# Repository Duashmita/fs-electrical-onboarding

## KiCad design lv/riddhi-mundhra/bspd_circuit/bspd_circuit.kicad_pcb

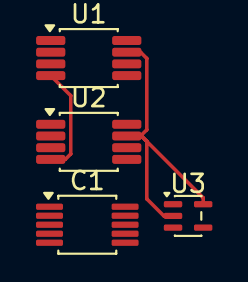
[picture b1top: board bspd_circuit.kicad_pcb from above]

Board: 2 copper layers, 4 parts (0 on the bottom side), 6 nets.

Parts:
C1: 1000; MSOP-10_3x3mm_P0.5mm
U1, U2: OPA196xDGK; VSSOP-8_3x3mm_P0.65mm
U3: TLV172IDCK; SOT-353_SC-70-5

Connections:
+3V3: U1.4 (V-), U1.7 (V+), U2.4 (V-), U2.7 (V+), U3.2 (V-), U3.5 (V+)
unnamed: C1.2, U3.4
unnamed: U1.3 (+), U2.3 (+)
unnamed: U1.2 (-), U2.2 (-)
unnamed: U1.6, U2.6
unnamed: C1.1, U3.3 (-)

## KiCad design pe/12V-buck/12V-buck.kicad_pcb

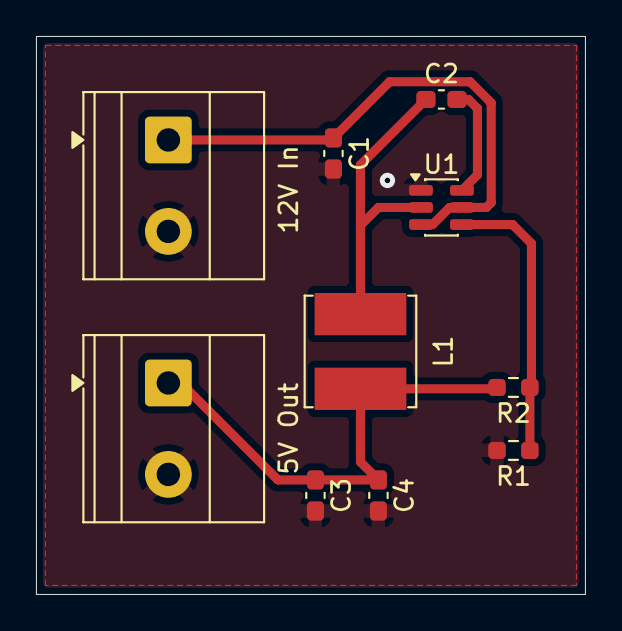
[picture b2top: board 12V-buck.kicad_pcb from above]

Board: 2 copper layers, 30.5 x 31.0 mm, 10 parts (0 on the bottom side), 6 nets.

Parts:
5V Out: 5V; TerminalBlock_Phoenix_MKDS-1,5-2-5.08_1x02_P5.08mm_Horizont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
12V In: 12V; TerminalBlock_Phoenix_MKDS-1,5-2-5.08_1x02_P5.08mm_Horizont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
C1: 10uF; C_0603_1608Metric_Pad1.08x0.95mm_HandSolder
C2: 100nF; C_0603_1608Metric_Pad1.08x0.95mm_HandSolder
C3, C4: 22uF; C_0603_1608Metric_Pad1.08x0.95mm_HandSolder
L1: 3.3uH; L_Bourns_SRN6045TA
R1: 10k; R_0603_1608Metric_Pad0.98x0.95mm_HandSolder
R2: 54.9k; R_0603_1608Metric_Pad0.98x0.95mm_HandSolder
U1: TPS563208; SOT-23-6

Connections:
+5V: 5V Out.1, C3.1, C4.1, L1.2, R2.2
+12V: 12V In.1, C1.1, U1.3 (VIN), U1.5 (EN)
GND: 5V Out.2, 12V In.2, C1.2, C3.2, C4.2, R1.2, U1.1 (GND)
unnamed: C2.1, L1.1, U1.2 (SW)
unnamed: C2.2, U1.6 (VBST)
unnamed: R1.1, R2.1, U1.4 (VFB)

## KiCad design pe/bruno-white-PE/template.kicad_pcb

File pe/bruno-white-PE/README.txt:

KiCad Local History Directory
=============================

Hello Edmund, this is the link to my google document here:

https://docs.google.com/document/d/1SfllieP0r4iqk_yWfgpT94NKgeAnDmSCqJz-1QESXFs/edit?usp=sharing

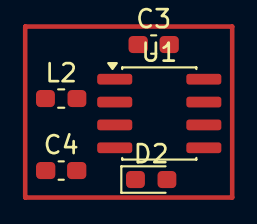
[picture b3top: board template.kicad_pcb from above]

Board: 2 copper layers, 5 parts (0 on the bottom side), 4 nets, no tracks yet.

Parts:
C3, C4: C_Small; C_0603_1608Metric_Pad1.08x0.95mm_HandSolder
D2: D_Small; D_0603_1608Metric_Pad1.05x0.95mm_HandSolder
L2: 2A; L_0603_1608Metric_Pad1.05x0.95mm_HandSolder
U1: XL1509-ADJ; SOIC-8_3.9x4.9mm_P1.27mm

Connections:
/VIN: C3.1, U1.1 (VIN)
/VOUT: C4.1, L2.2
GND: C3.2, C4.2, D2.2 (A), U1.5 (GND), U1.6 (GND), U1.7 (GND), U1.8 (GND)
unnamed: D2.1 (K), L2.1, U1.2 (OUT)

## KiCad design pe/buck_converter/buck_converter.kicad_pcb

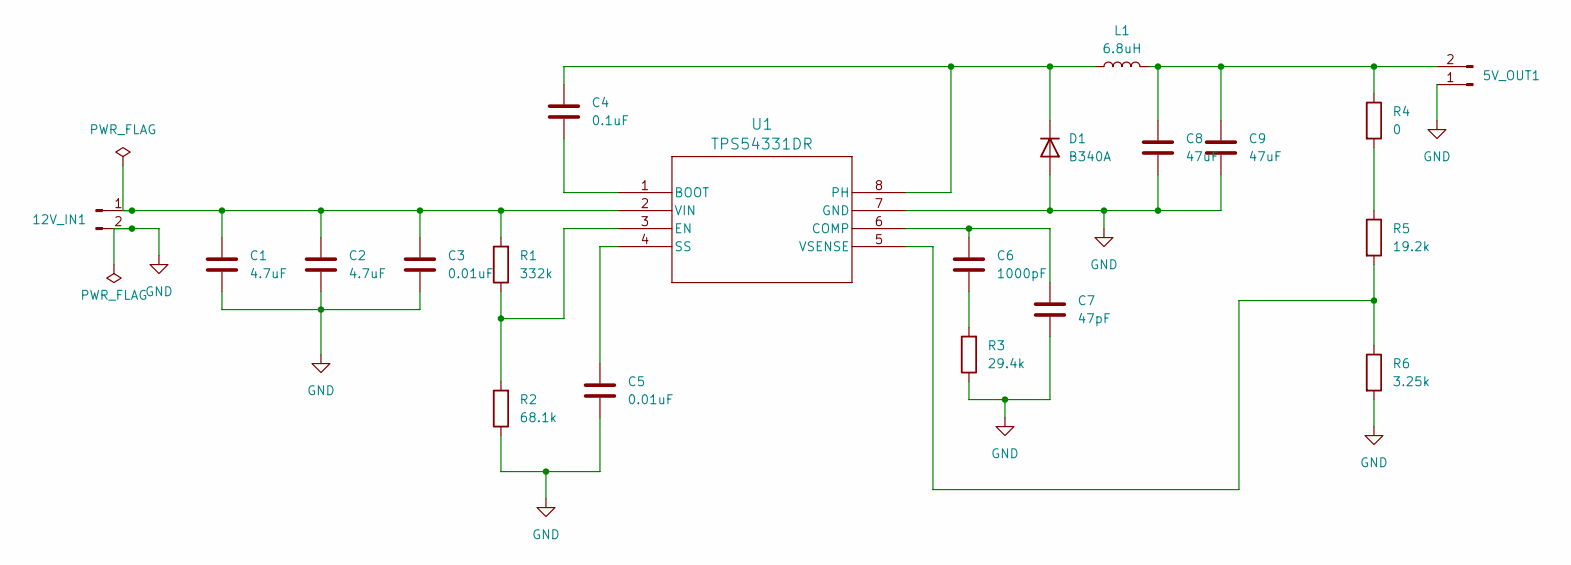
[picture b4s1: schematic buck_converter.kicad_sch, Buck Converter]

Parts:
5V_OUT1, 12V_IN1: 12V_IN; PinHeader_1x02_P2.54mm_Vertical
C1, C2: 4.7uF; C_1206_3216Metric_Pad1.33x1.80mm_HandSolder; Digikey Part Number C3216X7R1E475K160AC
C3, C5: 0.01uF; C_0201_0603Metric_Pad0.64x0.40mm_HandSolder; Digikey Part Number C0603C103K5RACTU
C4: 0.1uF; C_0201_0603Metric_Pad0.64x0.40mm_HandSolder; Digikey Part Number C0603C104K5RACTU
C6: 1000pF; C_0201_0603Metric_Pad0.64x0.40mm_HandSolder; Digikey Part Number C1608C0G1H472J080AA
C7: 47pF; C_0201_0603Metric_Pad0.64x0.40mm_HandSolder; Digikey Part Number C0603C390J5GACTU
C8, C9: 47uF; C_1210_3225Metric_Pad1.33x2.70mm_HandSolder; Digikey Part Number C3225X5R1A336M200AC
D1: B340A; D_SMA_Handsoldering; Digikey Part Number B340A-13-F
L1: 6.8uH; L_Bourns-SRN8040_8x8.15mm; Digikey Part Number SRN8040-6R8Y
R1: 332k; R_0201_0603Metric_Pad0.64x0.40mm_HandSolder; Digikey Part Number RC0603FR-07332KL
R2: 68.1k; R_0201_0603Metric_Pad0.64x0.40mm_HandSolder; Digikey Part Number RC0603FR-0768K1L
R3: 29.4k; R_0201_0603Metric_Pad0.64x0.40mm_HandSolder; Digikey Part Number RC0603FR-0749K9L
R4: 0; R_0201_0603Metric_Pad0.64x0.40mm_HandSolder; Digikey Part Number RC0603JR-070RL
R5: 19.2k; R_0201_0603Metric_Pad0.64x0.40mm_HandSolder; Digikey Part Number AC0603FR-0710KL
R6: 3.25k; R_0201_0603Metric_Pad0.64x0.40mm_HandSolder; Digikey Part Number RC0603FR-071K91L
U1: TPS54331DR; SOIC-8_3.9x4.9mm_P1.27mm; Digikey Part Number TPS54331DR

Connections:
GND: 5V_OUT1.1, 12V_IN1.2, C1.2, C2.2, C3.2, C5.2, C7.2, C8.2, C9.2, D1.2 (A), R2.1, R3.1, R6.2, U1.7 (GND)
unnamed: 5V_OUT1.2, C8.1, C9.1, L1.2, R4.1
unnamed: 12V_IN1.1, C1.1, C2.1, C3.1, R1.2, U1.2 (VIN)
unnamed: C6.2, R3.2
unnamed: C4.1, D1.1 (K), L1.1, U1.8 (PH)
unnamed: R4.2, R5.1
unnamed: C4.2, U1.1 (BOOT)
unnamed: C6.1, C7.1, U1.6 (COMP)
unnamed: R1.1, R2.2, U1.3 (EN)
unnamed: C5.1, U1.4 (SS)
unnamed: R5.2, R6.1, U1.5 (VSENSE)

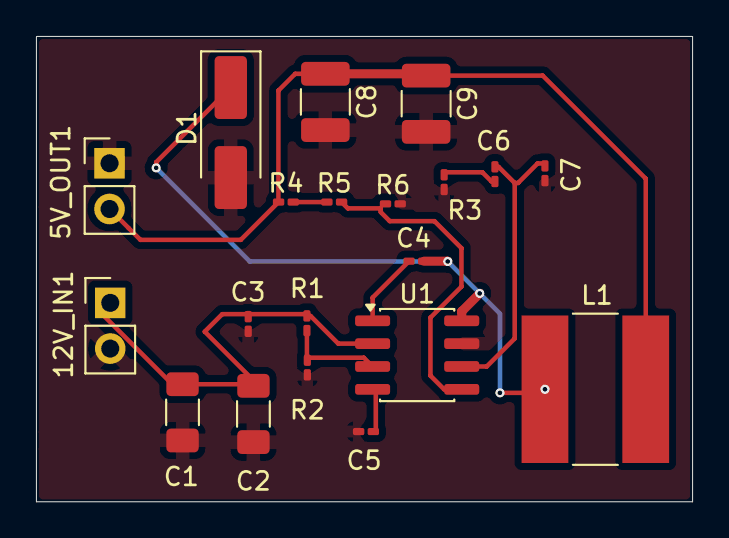
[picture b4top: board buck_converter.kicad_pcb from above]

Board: 2 copper layers, 36.4 x 25.8 mm, 20 parts (0 on the bottom side), 11 nets.

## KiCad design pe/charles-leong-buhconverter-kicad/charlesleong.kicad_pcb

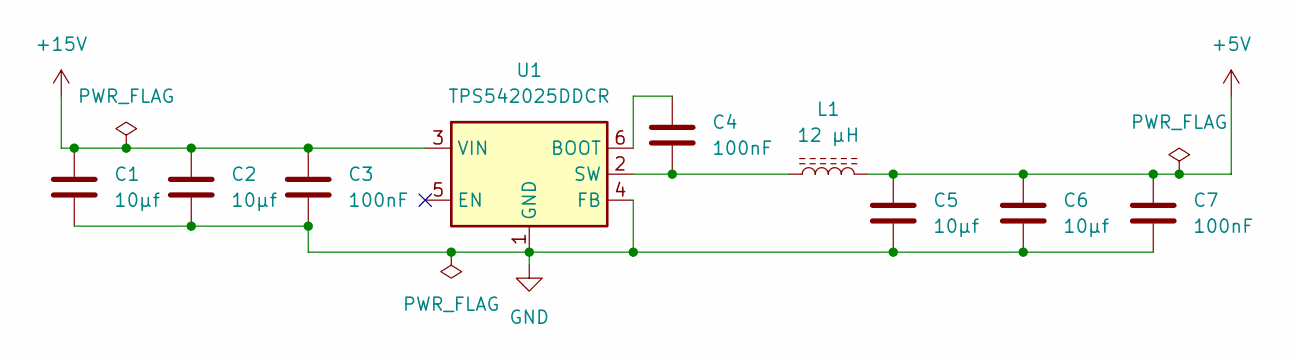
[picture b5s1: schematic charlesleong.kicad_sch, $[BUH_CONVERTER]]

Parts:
C1, C2, C5, C6: 10μf; C_2220_5750Metric_Pad1.97x5.40mm_HandSolder; Manufacturer Part Number 22201C106MAT2A; Digikey Part Number 478-KGM55DR72A106MVDKR-ND
C3, C4, C7: 100nF; C_1210_3225Metric_Pad1.33x2.70mm_HandSolder; Manufacturer Part Number C1210C104K5GACTU; Digikey Part Number 399-C1210C104K5GACTUDKR-ND
L1: 12 µH; L_Wurth_WE-PD2SR-7850; Manufacturer Part Number 744787120; Digikey Part Number 732-4529-6-ND
U1: TPS542025DDCR; SOT-23-6; Manufacturer Part Number TPS542025DDCR; Digikey Part Number 296-TPS542025DDCRDKR-ND

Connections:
+5V: C5.1, C6.1, C7.1, L1.2
+15V: C1.1, C2.1, C3.1, U1.3 (VIN)
GND: C1.2, C2.2, C3.2, C5.2, C6.2, C7.2, U1.1 (GND), U1.4 (FB)
unnamed: C4.1, U1.6 (BOOT)
unnamed: C4.2, L1.1, U1.2 (SW)

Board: 2 copper layers, 9 parts (0 on the bottom side), 5 nets, no tracks yet.
